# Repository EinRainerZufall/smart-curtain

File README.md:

# A smal but fast smart curtain.

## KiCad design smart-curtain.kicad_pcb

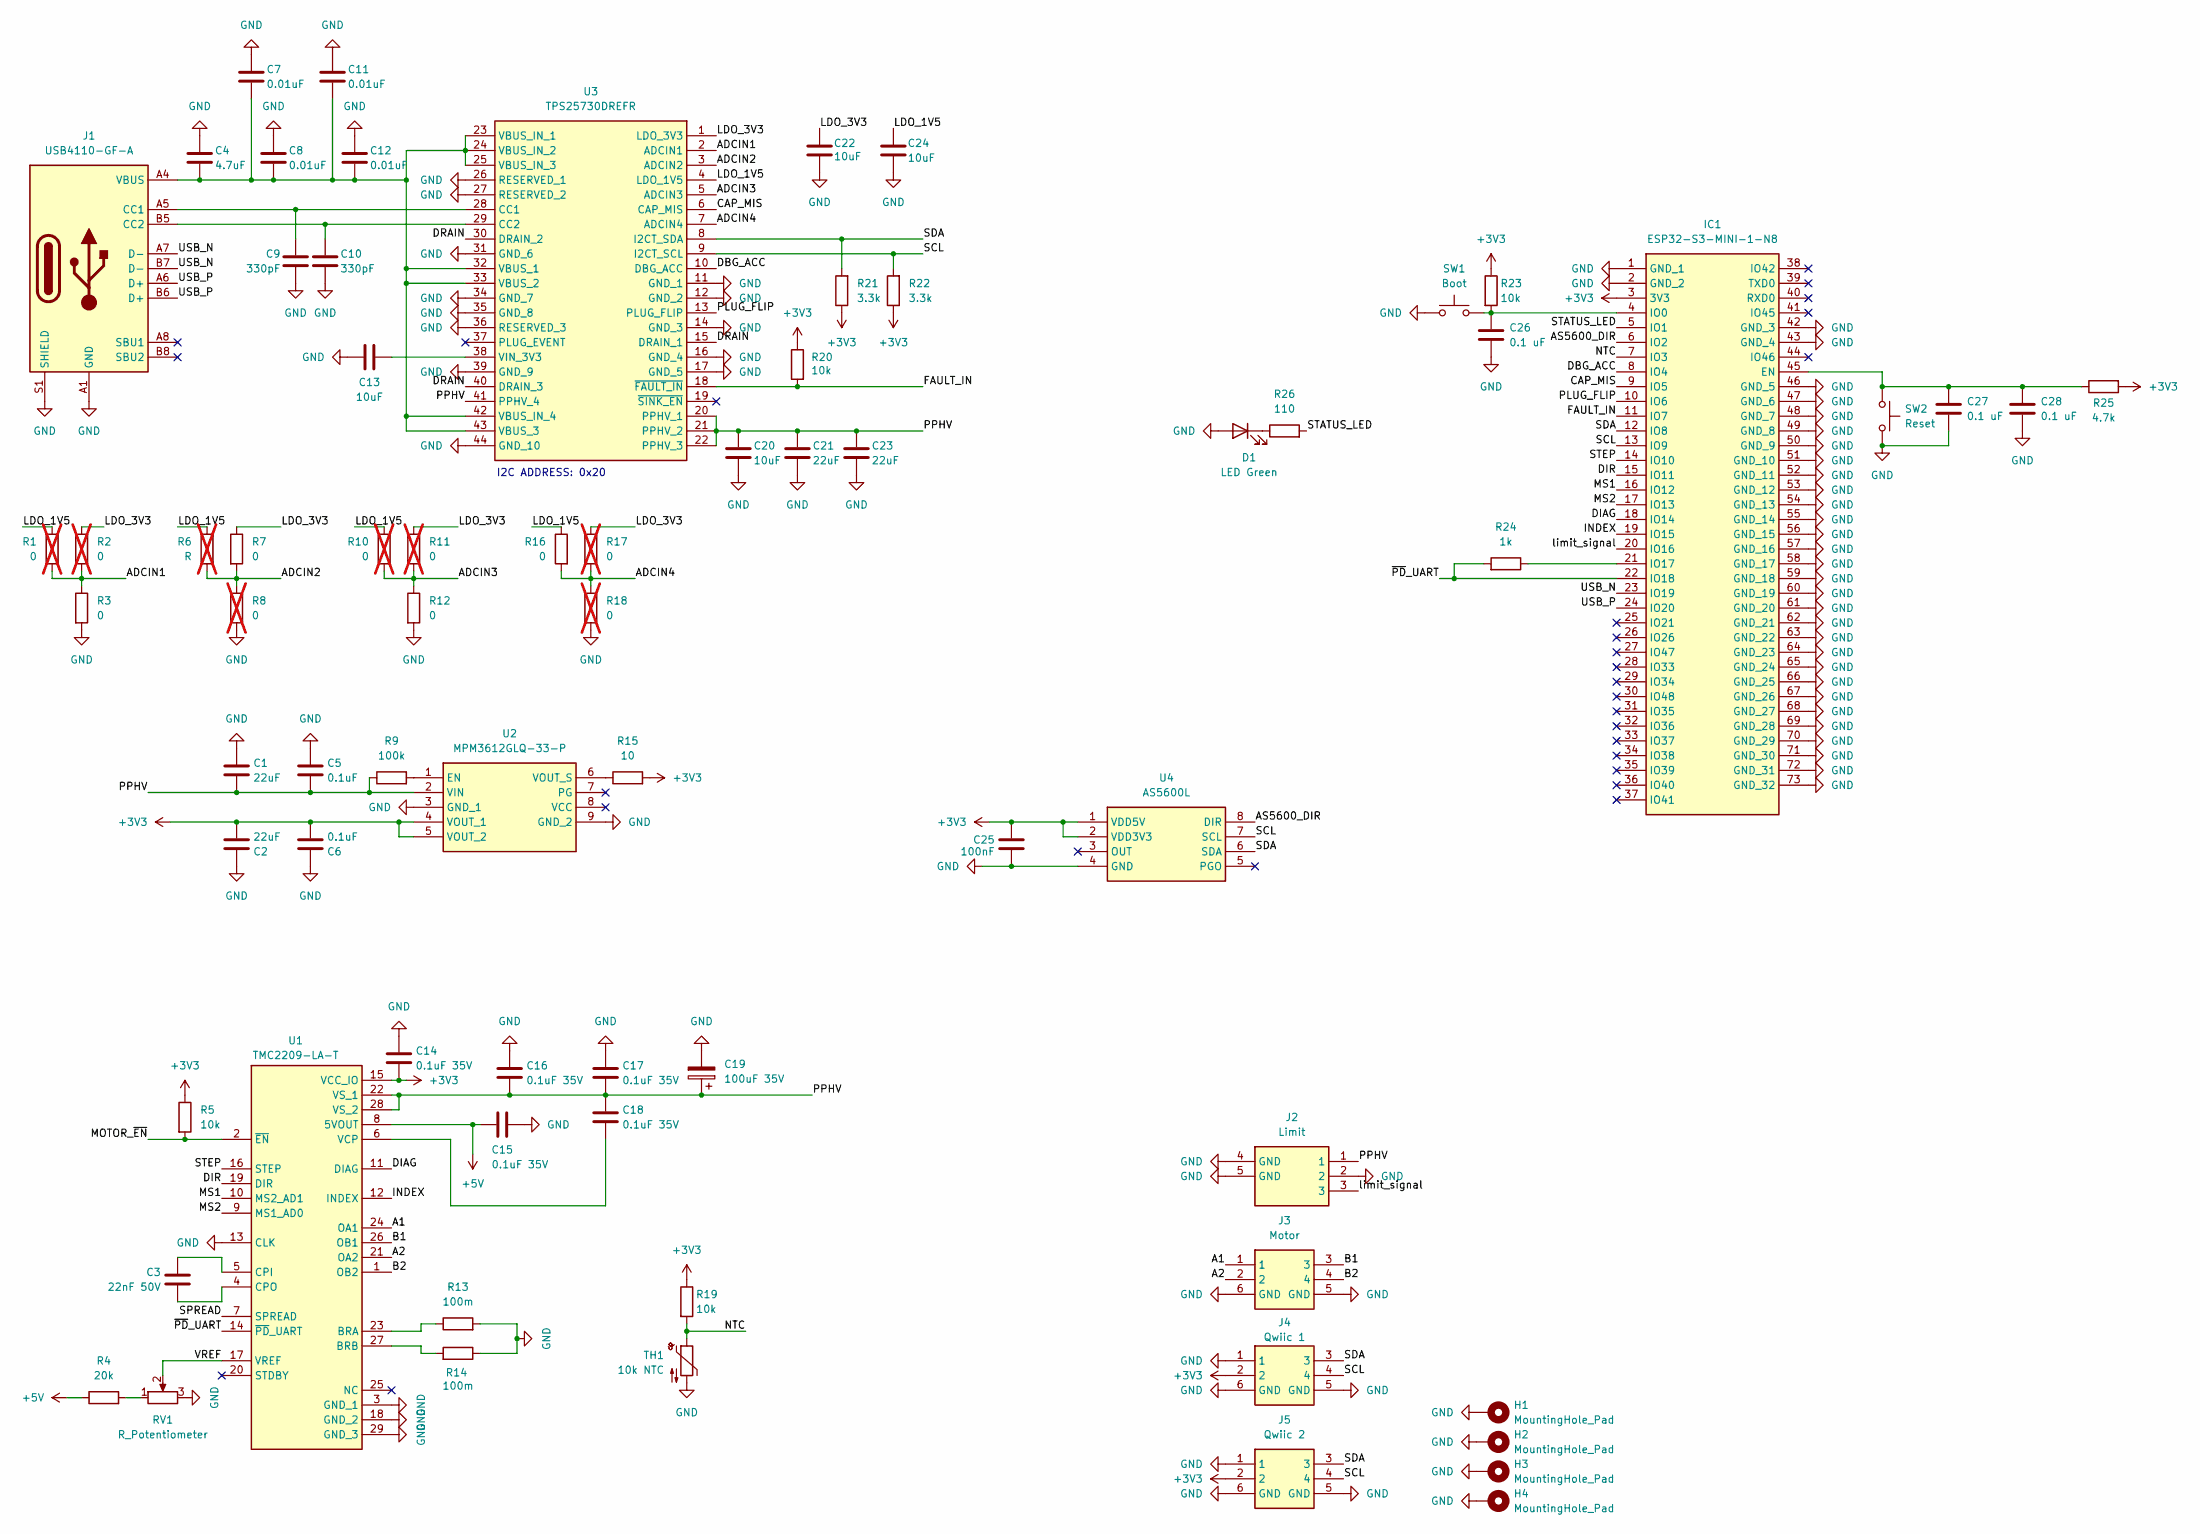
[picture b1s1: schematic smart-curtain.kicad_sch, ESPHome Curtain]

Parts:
C1, C2, C21, C23: 22uF; C_0402_1005Metric
C3: 22nF 50V; C_0402_1005Metric
C4: 4.7uF; C_0402_1005Metric
C5, C6: 0.1uF; C_0402_1005Metric
C7, C8, C11, C12: 0.01uF; C_0402_1005Metric
C9, C10: 330pF; C_0402_1005Metric
C13, C20, C22, C24: 10uF; C_0402_1005Metric
C14, C15, C16, C17, C18: 0.1uF 35V; C_0402_1005Metric
C19: 100uF 35V; CP_Elec_4x3
C25: 100nF; C_0402_1005Metric
C26, C27, C28: 0.1 uF; C_0402_1005Metric
D1: LED Green; D_0402_1005Metric
H1, H2, H3, H4: MountingHole_Pad; MountingHole_3.2mm_M3_Pad_Via
IC1: ESP32-S3-MINI-1-N8; ESP32S3MINI1N8; Mouser Part Number 356-ESP32-S3-MINI1N8
J1: USB4110-GF-A; USB4110GFA; Mouser Part Number 640-USB4110-GF-A
J2: Limit; SM03BSRSSTBLFSN; Mouser Part Number N/A
J3: Motor; SM04B-SRSS-TB_LFSN_; Mouser Part Number 306-SM04BSRSSTBLFSN
J4: Qwiic 1; SM04B-SRSS-TB_LFSN_; Mouser Part Number 306-SM04BSRSSTBLFSN
J5: Qwiic 2; SM04B-SRSS-TB_LFSN_; Mouser Part Number 306-SM04BSRSSTBLFSN
R1, R2, R8, R10, R11, R17, R18: 0; R_0402_1005Metric; not fitted
R3, R7, R12, R16: 0; R_0402_1005Metric
R4: 20k; R_0402_1005Metric
R5, R19, R20, R23: 10k; R_0402_1005Metric
R6: R; R_0402_1005Metric; not fitted
R9: 100k; R_0402_1005Metric
R13, R14: 100m; R_0402_1005Metric
R15: 10; R_0402_1005Metric
R21, R22: 3.3k; R_0402_1005Metric
R24: 1k; R_0402_1005Metric
R25: 4.7k; R_0402_1005Metric
R26: 110; R_0402_1005Metric
RV1: R_Potentiometer; Potentiometer_Bourns_3214W_Vertical
SW1: Boot; SW_Push_1P1T_NO_CK_KMR2
SW2: Reset; SW_Push_1P1T_NO_CK_KMR2
TH1: 10k NTC; R_0402_1005Metric; Manufacturer_Part_Number NTCG103JX103DTDS
U1: TMC2209-LA-T; QFN50P500X500X90-29N-D; Mouser Part Number 700-TMC2209-LA-T
U2: MPM3612GLQ-33-P; MPM3612GLQ33P; Manufacturer_Part_Number MPM3612GLQ-33-P
U3: TPS25730DREFR; Mouser Part Number 595-TPS25730DREFR
U4: AS5600L; SOIC127P600X175-8N; Mouser Part Number 985-AS5600L-ASOM

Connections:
+3V3: C2.2, C6.2, C14.2, C25.1, IC1.3 (3V3), J4.2, J5.2, R5.1, R15.2, R19.1, R20.1, R21.1, R22.1, R23.1, R25.2, U1.15 (VCC_IO), U2.4 (VOUT_1), U2.5 (VOUT_2), U4.1 (VDD5V), U4.2 (VDD3V3)
+5V: C15.2, R4.1, U1.8 (5VOUT)
/A1: J3.1, U1.24 (OA1)
/A2: J3.2, U1.21 (OA2)
/ADCIN1: R1.2, R2.2, R3.1, U3.2 (ADCIN1)
/ADCIN2: R6.2, R7.2, R8.1, U3.3 (ADCIN2)
/ADCIN3: R10.2, R11.2, R12.1, U3.5 (ADCIN3)
/ADCIN4: R16.2, R17.2, R18.1, U3.7 (ADCIN4)
/AS5600_DIR: IC1.6 (IO2), U4.8 (DIR)
/B1: J3.3, U1.26 (OB1)
/B2: J3.4, U1.1 (OB2)
/CAP_MIS: IC1.9 (IO5), U3.6 (CAP_MIS)
/DBG_ACC: IC1.8 (IO4), U3.10 (DBG_ACC)
/DIAG: IC1.18 (IO14), U1.11 (DIAG)
/DIR: IC1.15 (IO11), U1.19 (DIR)
/DRAIN: U3.15 (DRAIN_1), U3.30 (DRAIN_2), U3.40 (DRAIN_3)
/FAULT_IN: IC1.11 (IO7), R20.2, U3.18 (~FAULT_IN)
/INDEX: IC1.19 (IO15), U1.12 (INDEX)
/LDO_1V5: C24.2, R1.1, R6.1, R10.1, R16.1, U3.4 (LDO_1V5)
/LDO_3V3: C22.2, R2.1, R7.1, R11.1, R17.1, U3.1 (LDO_3V3)
/MOTOR_~EN: R5.2, U1.2 (~EN)
/MS1: IC1.16 (IO12), U1.10 (MS2_AD1)
/MS2: IC1.17 (IO13), U1.9 (MS1_AD0)
/NTC: IC1.7 (IO3), R19.2, TH1.1
/PLUG_FLIP: IC1.10 (IO6), U3.13 (PLUG_FLIP)
/PPHV: C1.2, C5.2, C16.2, C17.2, C18.1, C19.1, C20.1, C21.1, C23.1, J2.1, R9.1, U1.22 (VS_1), U1.28 (VS_2), U2.2 (VIN), U3.20 (PPHV_1), U3.21 (PPHV_2), U3.22 (PPHV_3), U3.41 (PPHV_4)
/SCL: IC1.13 (IO9), J4.4, J5.4, R22.2, U3.9 (I2CT_SCL), U4.7 (SCL)
/SDA: IC1.12 (IO8), J4.3, J5.3, R21.2, U3.8 (I2CT_SDA), U4.6 (SDA)
/SPREAD: U1.7 (SPREAD)
/STATUS_LED: IC1.5 (IO1), R26.2
/STEP: IC1.14 (IO10), U1.16 (STEP)
/USB_N: IC1.23 (IO19), J1.A7 (D-), J1.B7 (D-)
/USB_P: IC1.24 (IO20), J1.A6 (D+), J1.B6 (D+)
/VREF: RV1.2, U1.17 (VREF)
/limit_signal: IC1.20 (IO16), J2.3
/~PD_UART: IC1.22 (IO18), R24.2, U1.14 (~PD_UART)
GND: C1.1, C2.1, C4.1, C5.1, C6.1, C7.1, C8.1, C9.2, C10.2, C11.1, C12.1, C13.1, C14.1, C15.1, C16.1, C17.1, C19.2, C20.2, C21.2, C22.1, C23.2, C24.1, C25.2, C26.2, C27.2, C28.2, D1.2 (A), H1.1, H2.1, H3.1, H4.1, IC1.1 (GND_1), IC1.2 (GND_2), IC1.42 (GND_3), IC1.43 (GND_4), IC1.46 (GND_5), IC1.47 (GND_6), IC1.48 (GND_7), IC1.49 (GND_8), IC1.50 (GND_9), IC1.51 (GND_10), IC1.52 (GND_11), IC1.53 (GND_12), IC1.54 (GND_13), IC1.55 (GND_14), IC1.56 (GND_15), IC1.57 (GND_16), IC1.58 (GND_17), IC1.59 (GND_18), IC1.60 (GND_19), IC1.61 (GND_20), IC1.62 (GND_21), IC1.63 (GND_22), IC1.64 (GND_23), IC1.65 (GND_24), IC1.66 (GND_25), IC1.67 (GND_26), IC1.68 (GND_27), IC1.69 (GND_28), IC1.70 (GND_29), IC1.71 (GND_30), IC1.72 (GND_31), IC1.73 (GND_32), J1.A1 (GND), J1.A12 (GND), J1.B1 (GND), J1.B12 (GND), J1.S1 (SHIELD), J2.2, J2.4 (GND), J2.5 (GND), J3.5 (GND), J3.6 (GND), J4.1, J4.5 (GND), J4.6 (GND), J5.1, J5.5 (GND), J5.6 (GND), R3.2, R8.2, R12.2, R13.2, R14.1, R18.2, RV1.3, SW1.1, SW2.2, TH1.2, U1.3 (GND_1), U1.13 (CLK), U1.18 (GND_2), U1.29 (GND_3), U2.3 (GND_1), U2.9 (GND_2), U3.11 (GND_1), U3.12 (GND_2), U3.14 (GND_3), U3.16 (GND_4), U3.17 (GND_5), U3.26 (RESERVED_1), U3.27 (RESERVED_2), U3.31 (GND_6), U3.34 (GND_7), U3.35 (GND_8), U3.36 (RESERVED_3), U3.39 (GND_9), U3.44 (GND_10), U4.4 (GND)
unnamed: D1.1 (K), R26.1
unnamed: C27.1, C28.1, IC1.45 (EN), R25.1, SW2.1
unnamed: C26.1, IC1.4 (IO0), R23.2, SW1.2
unnamed: IC1.21 (IO17), R24.1
unnamed: C9.1, J1.A5 (CC1), U3.28 (CC1)
unnamed: C10.1, J1.B5 (CC2), U3.29 (CC2)
unnamed: R4.2, RV1.1
unnamed: R13.1, U1.23 (BRA)
unnamed: R14.2, U1.27 (BRB)
unnamed: C3.1, U1.5 (CPI)
unnamed: C3.2, U1.4 (CPO)
unnamed: C18.2, U1.6 (VCP)
unnamed: R9.2, U2.1 (EN)
unnamed: R15.1, U2.6 (VOUT_S)
unnamed: C4.2, C7.2, C8.2, C11.2, C12.2, J1.A4 (VBUS), J1.A9 (VBUS), J1.B4 (VBUS), J1.B9 (VBUS), U3.23 (VBUS_IN_1), U3.24 (VBUS_IN_2), U3.25 (VBUS_IN_3), U3.32 (VBUS_1), U3.33 (VBUS_2), U3.42 (VBUS_IN_4), U3.43 (VBUS_3)
unnamed: C13.2, U3.38 (VIN_3V3)

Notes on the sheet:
I2C ADDRESS: 0x20

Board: 4 copper layers, 73 parts (1 on the bottom side), 52 nets, no tracks yet.

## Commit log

2025-10-26 Update smart-curtain.kicad_sch
    Connect labels to ESP pin`s
2025-10-26 Add AS5600
2025-11-01 swap B1 with A2
2025-11-01 swap J2 with J3
